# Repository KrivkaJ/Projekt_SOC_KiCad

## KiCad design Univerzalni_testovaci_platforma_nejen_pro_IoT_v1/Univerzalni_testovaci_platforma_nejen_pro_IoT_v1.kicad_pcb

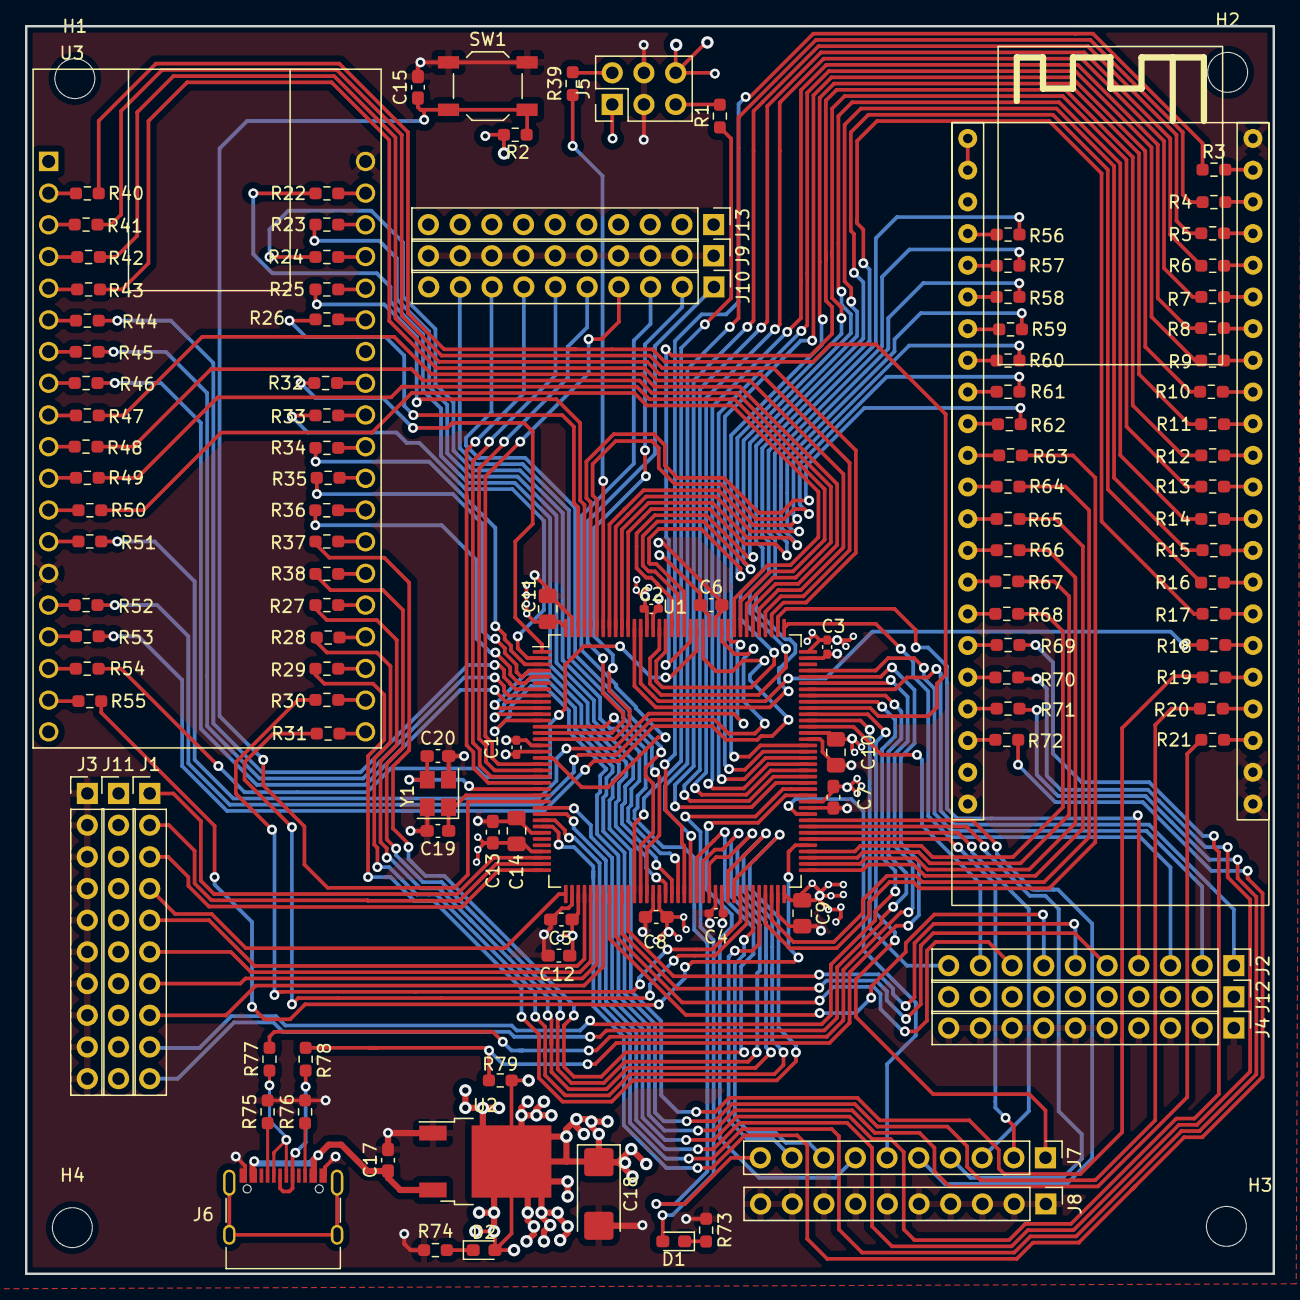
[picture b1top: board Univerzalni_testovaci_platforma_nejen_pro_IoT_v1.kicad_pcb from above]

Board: 4 copper layers, 100.0 x 100.0 mm, 123 parts (0 on the bottom side), 197 nets.

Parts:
C1, C2, C3, C4: 10nF; C_0402_1005Metric_Pad0.74x0.62mm_HandSolder
C5, C6, C7, C8: 10nF; C_0603_1608Metric_Pad1.08x0.95mm_HandSolder
C9, C10, C11, C14: 10nF; C_0805_2012Metric_Pad1.18x1.45mm_HandSolder
C12, C15: 4.7uF; C_0603_1608Metric_Pad1.08x0.95mm_HandSolder
C13: 1uF; C_0603_1608Metric_Pad1.08x0.95mm_HandSolder
C17: 22uF; C_0603_1608Metric_Pad1.08x0.95mm_HandSolder
C18: 22µF solid tantalum; CP_EIA-6032-20_AVX-F_Pad2.25x2.35mm_HandSolder
C19, C20: 18pF; C_0603_1608Metric_Pad1.08x0.95mm_HandSolder
D1, D2: RED; LED_0603_1608Metric_Pad1.05x0.95mm_HandSolder
H1, H2, H3, H4: MountingHole; MountingHole_3.2mm_M3
J1, J2, J3, J4, J7, J8, J9, J10, J11, J12, J13: Conn_01x10_Male; PinHeader_1x10_P2.54mm_Vertical
J5: Conn_02x03_Counter_Clockwise; PinHeader_2x03_P2.54mm_Vertical
J6: USB_C_Receptacle; USB_C_Receptacle_XKB_U262-16XN-4BVC11
R1, R39: 100k; R_0603_1608Metric_Pad0.98x0.95mm_HandSolder
R2: 10k; R_0603_1608Metric_Pad0.98x0.95mm_HandSolder
R3, R4, R5, R6, R7, R8, R9, R10, R11, R12, R13, R14, R15, R16, R17, R18, R19, R20, R21, R22, R23, R24, R25, R26, R27, R28, R29, R30, R31, R32, R33, R34, R35, R36, R37, R38, R40, R41, R42, R43, R44, R45, R46, R47, R48, R49, R50, R51, R52, R53, R54, R55, R56, R57, R58, R59, R60, R61, R62, R63, R64, R65, R66, R67, R68, R69, R70, R71, R72: 220R; R_0603_1608Metric_Pad0.98x0.95mm_HandSolder
R73, R74, R79: 1k5; R_0603_1608Metric_Pad0.98x0.95mm_HandSolder
R75, R76: 5k1; R_0603_1608Metric_Pad0.98x0.95mm_HandSolder
R77, R78: 20R; R_0603_1608Metric_Pad0.98x0.95mm_HandSolder
SW1: SW_Push_Dual; SW_SPST_TL3342
U1: STM32F103ZETx; LQFP-144_20x20mm_P0.5mm
U2: AMS1117-3.3; TO-252-2
U3: ESP32-DEVKITC-32D; MODULE_ESP32-DEVKITC-32D
U4: ESP32-S3; ESP32-devkit_v1
Y1: 12Mhz; Crystal_SMD_3225-4Pin_3.2x2.5mm

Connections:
+3.3VA: C13.1, C14.1, U1.33 (VDDA)
+3V3: C1.1, C2.1, C3.1, C4.1, C5.1, C6.1, C7.1, C8.1, C9.1, C10.1, C11.1, C12.1, C18.1, D2.2 (A), J5.1, J5.6, J11.1, J11.2, J11.3, J11.4, J11.5, J11.6, J11.7, J11.8, J11.9, J11.10, J12.1, J12.2, J12.3, J12.4, J12.5, J12.6, J12.7, J12.8, J12.9, J12.10, J13.1, J13.2, J13.3, J13.4, J13.5, J13.6, J13.7, J13.8, J13.9, J13.10, R2.1, R79.1, U1.17 (VDD), U1.39 (VDD), U1.52 (VDD), U1.62 (VDD), U1.72 (VDD), U1.84 (VDD), U1.95 (VDD), U1.108 (VDD), U1.121 (VDD), U1.131 (VDD), U1.144 (VDD), U2.2 (VO)
+5V: C17.1, J6.A4 (VBUS), J6.A9 (VBUS), J6.B4 (VBUS), J6.B9 (VBUS), U2.3 (VI)
/BOOT0: R39.1, U1.138 (BOOT0)
/ESP DEV_KIT J2 pin2: R40.2, U3.J2-2 (EN)
/ESP DEV_KIT J2 pin3: R41.2, U3.J2-3 (SENSOR_VP)
/ESP DEV_KIT J2 pin4: R42.2, U3.J2-4 (SENSOR_VN)
/ESP DEV_KIT J2 pin5: R43.2, U3.J2-5 (IO34)
/ESP DEV_KIT J2 pin6: R44.2, U3.J2-6 (IO35)
/ESP DEV_KIT J2 pin7: R45.2, U3.J2-7 (IO32)
/ESP DEV_KIT J2 pin8: R46.2, U3.J2-8 (IO33)
/ESP DEV_KIT J2 pin9: R47.2, U3.J2-9 (IO25)
/ESP DEV_KIT J2 pin10: R48.2, U3.J2-10 (IO26)
/ESP DEV_KIT J2 pin11: R49.2, U3.J2-11 (IO27)
/ESP DEV_KIT J2 pin12: R50.2, U3.J2-12 (IO14)
/ESP DEV_KIT J2 pin13: R51.2, U3.J2-13 (IO12)
/ESP DEV_KIT J2 pin15: R52.2, U3.J2-15 (IO13)
/ESP DEV_KIT J2 pin16: R53.2, U3.J2-16 (SD2)
/ESP DEV_KIT J2 pin17: R54.2, U3.J2-17 (SD3)
/ESP DEV_KIT J2 pin18: R55.2, U3.J2-18 (CMD)
/ESP DEV_KIT J3 pin2: R22.1, U3.J3-2 (IO23)
/ESP DEV_KIT J3 pin3: R23.1, U3.J3-3 (IO22)
/ESP DEV_KIT J3 pin4: R24.1, U3.J3-4 (TXD0)
/ESP DEV_KIT J3 pin5: R25.1, U3.J3-5 (RXD0)
/ESP DEV_KIT J3 pin6: R26.1, U3.J3-6 (IO21)
/ESP DEV_KIT J3 pin8: R32.1, U3.J3-8 (IO19)
/ESP DEV_KIT J3 pin9: R33.1, U3.J3-9 (IO18)
/ESP DEV_KIT J3 pin10: R34.1, U3.J3-10 (IO5)
/ESP DEV_KIT J3 pin11: R35.1, U3.J3-11 (IO17)
/ESP DEV_KIT J3 pin12: R36.1, U3.J3-12 (IO16)
/ESP DEV_KIT J3 pin13: R37.1, U3.J3-13 (IO4)
/ESP DEV_KIT J3 pin14: R38.1, U3.J3-14 (IO0)
/ESP DEV_KIT J3 pin15: R27.1, U3.J3-15 (IO2)
/ESP DEV_KIT J3 pin16: R28.1, U3.J3-16 (IO15)
/ESP DEV_KIT J3 pin17: R29.1, U3.J3-17 (SD1)
/ESP DEV_KIT J3 pin18: R30.1, U3.J3-18 (SD0)
/ESP DEV_KIT J3 pin19: R31.1, U3.J3-19 (CLK)
/ESP S3 J1 pin4: R56.2, U4.4 (GPIO4)
/ESP S3 J1 pin5: R57.2, U4.5 (GPIO5)
/ESP S3 J1 pin6: R58.2, U4.6 (GPIO6)
/ESP S3 J1 pin7: R59.2, U4.7 (GPIO7)
/ESP S3 J1 pin8: R60.2, U4.8 (GPIO15-RTS0)
/ESP S3 J1 pin9: R61.2, U4.9 (GPIO16-CTS0)
/ESP S3 J1 pin10: R62.2, U4.10 (GPIO17-TX1)
/ESP S3 J1 pin11: R63.2, U4.11 (GPIO18-RX1)
/ESP S3 J1 pin12: R64.2, U4.12 (GPIO8)
/ESP S3 J1 pin13: R65.2, U4.13 (GPIO3!!!D)
/ESP S3 J1 pin14: R66.2, U4.14 (GPIO46!!!D)
/ESP S3 J1 pin15: R67.2, U4.15 (GPIO9)
/ESP S3 J1 pin16: R68.2, U4.16 (GPIO10)
/ESP S3 J1 pin17: R69.2, U4.17 (GPIO11)
/ESP S3 J1 pin18: R70.2, U4.18 (GPIO12)
/ESP S3 J1 pin19: R71.2, U4.19 (GPIO13)
/ESP S3 J1 pin20: R72.2, U4.20 (GPIO14)
/ESP S3 J3 pin2: R3.2, U4.24 (GPIO43-TX0)
/ESP S3 J3 pin3: R4.2, U4.25 (GPIO44-RX0)
/ESP S3 J3 pin4: R5.2, U4.26 (GPIO1)
/ESP S3 J3 pin5: R6.2, U4.27 (GPIO2)
/ESP S3 J3 pin6: R7.2, U4.28 (GPIO42)
/ESP S3 J3 pin7: R8.2, U4.29 (GPIO41)
/ESP S3 J3 pin8: R9.2, U4.30 (GPIO40)
/ESP S3 J3 pin9: R10.2, U4.31 (GPIO39)
/ESP S3 J3 pin10: R11.2, U4.32 (GPIO38)
/ESP S3 J3 pin11: R12.2, U4.33 (GPIO37)
/ESP S3 J3 pin12: R13.2, U4.34 (GPIO36)
/ESP S3 J3 pin13: R14.2, U4.35 (GPIO35)
/ESP S3 J3 pin14: R15.2, U4.36 (GPIO0!!!U)
/ESP S3 J3 pin15: R16.2, U4.37 (GPIO45!!!D)
/ESP S3 J3 pin16: R17.2, U4.38 (GPIO48)
/ESP S3 J3 pin17: R18.2, U4.39 (GPIO47)
/ESP S3 J3 pin18: R19.2, U4.40 (GPIO21)
/ESP S3 J3 pin19: R20.2, U4.41 (GPIO20-D+)
/ESP S3 J3 pin20: R21.2, U4.42 (GPIO19-D-)
BOOT1: R1.1, U1.48 (PB2)
GND: C1.2, C2.2, C3.2, C4.2, C5.2, C6.2, C7.2, C8.2, C9.2, C10.2, C11.2, C12.2, C13.2, C14.2, C15.2, C17.2, C18.2, C19.2, C20.2, J3.1, J3.2, J3.3, J3.4, J3.5, J3.6, J3.7, J3.8, J3.9, J3.10, J4.1, J4.2, J4.3, J4.4, J4.5, J4.6, J4.7, J4.8, J4.9, J4.10, J5.3, J5.4, J6.A1 (GND), J6.A12 (GND), J6.B1 (GND), J6.B12 (GND), J8.1, J8.2, J8.3, J8.4, J8.5, J8.6, J8.7, J8.8, J8.9, J8.10, J9.1, J9.2, J9.3, J9.4, J9.5, J9.6, J9.7, J9.8, J9.9, J9.10, R73.2, R74.2, R75.2, R76.2, SW1.1, U1.16 (VSS), U1.30 (VSSA), U1.38 (VSS), U1.51 (VSS), U1.61 (VSS), U1.71 (VSS), U1.83 (VSS), U1.94 (VSS), U1.107 (VSS), U1.120 (VSS), U1.130 (VSS), U1.143 (VSS), U2.1 (GND), U3.J2-14 (GND1), U3.J3-1 (GND3), U3.J3-7 (GND2), U4.22 (GND), U4.23 (GND), U4.43 (GND), U4.44 (GND), Y1.2, Y1.4
unnamed: C15.1, R2.2, SW1.2, U1.25 (NRST)
unnamed: D1.1 (K), R73.1
unnamed: D1.2 (A), U1.86 (PD15)
unnamed: D2.1 (K), R74.1
unnamed: J1.1, U1.34 (PA0)
unnamed: J1.2, U1.35 (PA1)
unnamed: J1.3, U1.36 (PA2)
unnamed: J1.4, U1.37 (PA3)
unnamed: J1.5, U1.40 (PA4)
unnamed: J1.6, U1.41 (PA5)
unnamed: J1.7, U1.42 (PA6)
unnamed: J1.8, U1.43 (PA7)
unnamed: J1.9, U1.100 (PA8)
unnamed: J1.10, U1.101 (PA9)
unnamed: J5.2, R39.2
unnamed: J5.5, R1.2
unnamed: J6.A5 (CC1), R75.1
unnamed: J6.A6 (D+), J6.B6 (D+), R78.1
unnamed: J6.A7 (D-), J6.B7 (D-), R77.1
unnamed: J6.B5 (CC2), R76.1
unnamed: R3.1, U1.56 (PG0)
unnamed: R4.1, U1.57 (PG1)
unnamed: R5.1, U1.87 (PG2)
unnamed: R6.1, U1.88 (PG3)
unnamed: R7.1, U1.89 (PG4)
unnamed: R8.1, U1.90 (PG5)
unnamed: R9.1, U1.91 (PG6)
unnamed: R10.1, U1.92 (PG7)
unnamed: R11.1, U1.93 (PG8)
unnamed: R12.1, U1.124 (PG9)
unnamed: R13.1, U1.125 (PG10)
unnamed: R14.1, U1.126 (PG11)
unnamed: R15.1, U1.127 (PG12)
unnamed: R16.1, U1.128 (PG13)
unnamed: R17.1, U1.129 (PG14)
unnamed: R18.1, U1.132 (PG15)
unnamed: R19.1, U1.10 (PF0)
unnamed: R20.1, U1.11 (PF1)
unnamed: R21.1, U1.12 (PF2)
unnamed: R22.2, U1.53 (PF13)
unnamed: R23.2, U1.54 (PF14)
unnamed: R24.2, U1.55 (PF15)
unnamed: R25.2, U1.141 (PE0)
unnamed: R26.2, U1.142 (PE1)
unnamed: R27.2, U1.60 (PE9)
unnamed: R28.2, U1.63 (PE10)
unnamed: R29.2, U1.64 (PE11)
unnamed: R30.2, U1.65 (PE12)
unnamed: R31.2, U1.66 (PE13)
unnamed: R32.2, U1.1 (PE2)
unnamed: R33.2, U1.2 (PE3)
unnamed: R34.2, U1.3 (PE4)
unnamed: R35.2, U1.4 (PE5)
unnamed: R36.2, U1.5 (PE6)
unnamed: R37.2, U1.58 (PE7)
unnamed: R38.2, U1.59 (PE8)
unnamed: R40.1, U1.99 (PC9)
unnamed: R41.1, U1.111 (PC10)
unnamed: R42.1, U1.112 (PC11)
unnamed: R43.1, U1.113 (PC12)
unnamed: R44.1, U1.7 (PC13)
unnamed: R45.1, U1.8 (PC14)
unnamed: R46.1, U1.9 (PC15)
unnamed: R47.1, U1.114 (PD0)
unnamed: R48.1, U1.115 (PD1)
unnamed: R49.1, U1.116 (PD2)
unnamed: R50.1, U1.117 (PD3)
unnamed: R51.1, U1.118 (PD4)
unnamed: R52.1, U1.119 (PD5)
unnamed: R53.1, U1.122 (PD6)
unnamed: R54.1, U1.123 (PD7)
unnamed: R55.1, U1.77 (PD8)
unnamed: R56.1, U1.133 (PB3)
unnamed: R57.1, U1.134 (PB4)
unnamed: R58.1, U1.135 (PB5)
unnamed: R59.1, U1.136 (PB6)
unnamed: R60.1, U1.137 (PB7)
unnamed: R61.1, U1.139 (PB8)
unnamed: R62.1, U1.140 (PB9)
unnamed: R63.1, U1.69 (PB10)
unnamed: R64.1, U1.70 (PB11)
unnamed: R65.1, U1.73 (PB12)
unnamed: R66.1, U1.74 (PB13)
unnamed: R67.1, U1.75 (PB14)
unnamed: R68.1, U1.76 (PB15)
unnamed: R69.1, U1.26 (PC0)
unnamed: R70.1, U1.27 (PC1)
unnamed: R71.1, U1.28 (PC2)
unnamed: R72.1, U1.29 (PC3)
OSC_IN: C20.1, U1.23 (RCC_OSC_IN), Y1.3
OSC_OUT: C19.1, U1.24 (RCC_OSC_OUT), Y1.1
PA10: J2.1, U1.102 (PA10)
PA13: J2.2, U1.105 (PA13)
PA14: J2.3, U1.109 (PA14)
PA15: J2.4, U1.110 (PA15)
PB0: J2.5, U1.46 (PB0)
PB1: J2.6, U1.47 (PB1)
PC4: J2.7, U1.44 (PC4)
PC5: J2.8, U1.45 (PC5)
PC6: J2.9, U1.96 (PC6)
PC7: J2.10, U1.97 (PC7)
PC8: J7.1, U1.98 (PC8)
PD9: J7.2, U1.78 (PD9)
PD10: J7.3, U1.79 (PD10)
PD11: J7.4, U1.80 (PD11)
PD12: J7.5, U1.81 (PD12)
PD13: J7.6, U1.82 (PD13)
PD14: J7.7, U1.85 (PD14)
PE14: J7.8, U1.67 (PE14)
PE15: J7.9, U1.68 (PE15)
PF3: J7.10, U1.13 (PF3)
PF4: J10.1, U1.14 (PF4)
PF5: J10.2, U1.15 (PF5)
PF6: J10.3, U1.18 (PF6)
PF7: J10.4, U1.19 (PF7)
PF8: J10.5, U1.20 (PF8)
PF9: J10.6, U1.21 (PF9)
PF10: J10.7, U1.22 (PF10)
PF11: J10.8, U1.49 (PF11)
PF12: J10.9, U1.50 (PF12)
USB_D+: R78.2, R79.2, U1.104 (PA12)
USB_D-: R77.2, U1.103 (PA11)

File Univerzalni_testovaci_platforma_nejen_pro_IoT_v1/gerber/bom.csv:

Comment,Designator,Footprint,LCSC
10nF,"C1,C2,C3,C4",Capacitor_SMD:C_0402_1005Metric_Pad0.74x0.62mm_HandSolder,C307331
10nF,"C5,C6,C7,C8",Capacitor_SMD:C_0603_1608Metric_Pad1.08x0.95mm_HandSolder,C14663
10nF,"C9,C10,C11,C14",Capacitor_SMD:C_0805_2012Metric_Pad1.18x1.45mm_HandSolder,C49678
4.7uF,"C12,C15",Capacitor_SMD:C_0603_1608Metric_Pad1.08x0.95mm_HandSolder,C19666
1uF,C13,Capacitor_SMD:C_0603_1608Metric_Pad1.08x0.95mm_HandSolder,C15849
22uF,C17,Capacitor_SMD:C_0603_1608Metric_Pad1.08x0.95mm_HandSolder,C59461
22µF solid tantalum,C18,Capacitor_Tantalum_SMD:CP_EIA-6032-20_AVX-F_Pad2.25x2.35mm_HandSolder,C2798049
18pF,"C19,C20",Capacitor_SMD:C_0603_1608Metric_Pad1.08x0.95mm_HandSolder,C1647
RED,"D1,D2",LED_SMD:LED_0603_1608Metric_Pad1.05x0.95mm_HandSolder,C2286
Conn_02x03_Counter_Clockwise,J5,Connector_PinHeader_2.54mm:PinHeader_2x03_P2.54mm_Vertical,C2894964
USB_C_Receptacle,J6,Connector_USB:USB_C_Receptacle_XKB_U262-16XN-4BVC11,C165948
100k,"R1,R39",Resistor_SMD:R_0603_1608Metric_Pad0.98x0.95mm_HandSolder,C25803
10k,R2,Resistor_SMD:R_0603_1608Metric_Pad0.98x0.95mm_HandSolder,C25804
220R,"R3,R4,R5,R6,R7,R8,R9,R10,R11,R12,R13,R14,R15,R16,R17,R18,R19,R20,R21,R22,R23,R24,R25,R26,R27,R28,R29,R30,R31,R32,R33,R34,R35,R36,R37,R38,R40,R41,R42,R43,R44,R45,R46,R47,R48,R49,R50,R51,R52,R53,R54,R55,R56,R57,R58,R59,R60,R61,R62,R63,R64,R65,R66,R67,R68,R69,R70,R71,R72",Resistor_SMD:R_0603_1608Metric_Pad0.98x0.95mm_HandSolder,C22962
1k5,"R73,R74,R79",Resistor_SMD:R_0603_1608Metric_Pad0.98x0.95mm_HandSolder,C22843
5k1,"R75,R76",Resistor_SMD:R_0603_1608Metric_Pad0.98x0.95mm_HandSolder,C23186
20R,"R77,R78",Resistor_SMD:R_0603_1608Metric_Pad0.98x0.95mm_HandSolder,C22950
SW_MEC_5E,SW1,,C318884
STM32F103ZETx,U1,Package_QFP:LQFP-144_20x20mm_P0.5mm,C8287
AMS1117-3.3,U2,Package_TO_SOT_SMD:TO-252-2,C841797
12Mhz,Y1,Crystal:Crystal_SMD_3225-4Pin_3.2x2.5mm,C9002

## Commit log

2023-11-29 add_project
2023-12-20 průběžná commit
2023-12-20 začátek hierarchických sheetů
2023-12-20 odstranění diakritiky z názvu
2023-12-21 průběžný commit
2024-01-25 schema hotovo
2024-01-26 asi hotovo
2024-01-26 uplně hotovo
2024-01-31 jdu to objednat
2024-02-24 změna usměrňovače napětí na správný
2024-02-26 změny schématu pro lepší focení
